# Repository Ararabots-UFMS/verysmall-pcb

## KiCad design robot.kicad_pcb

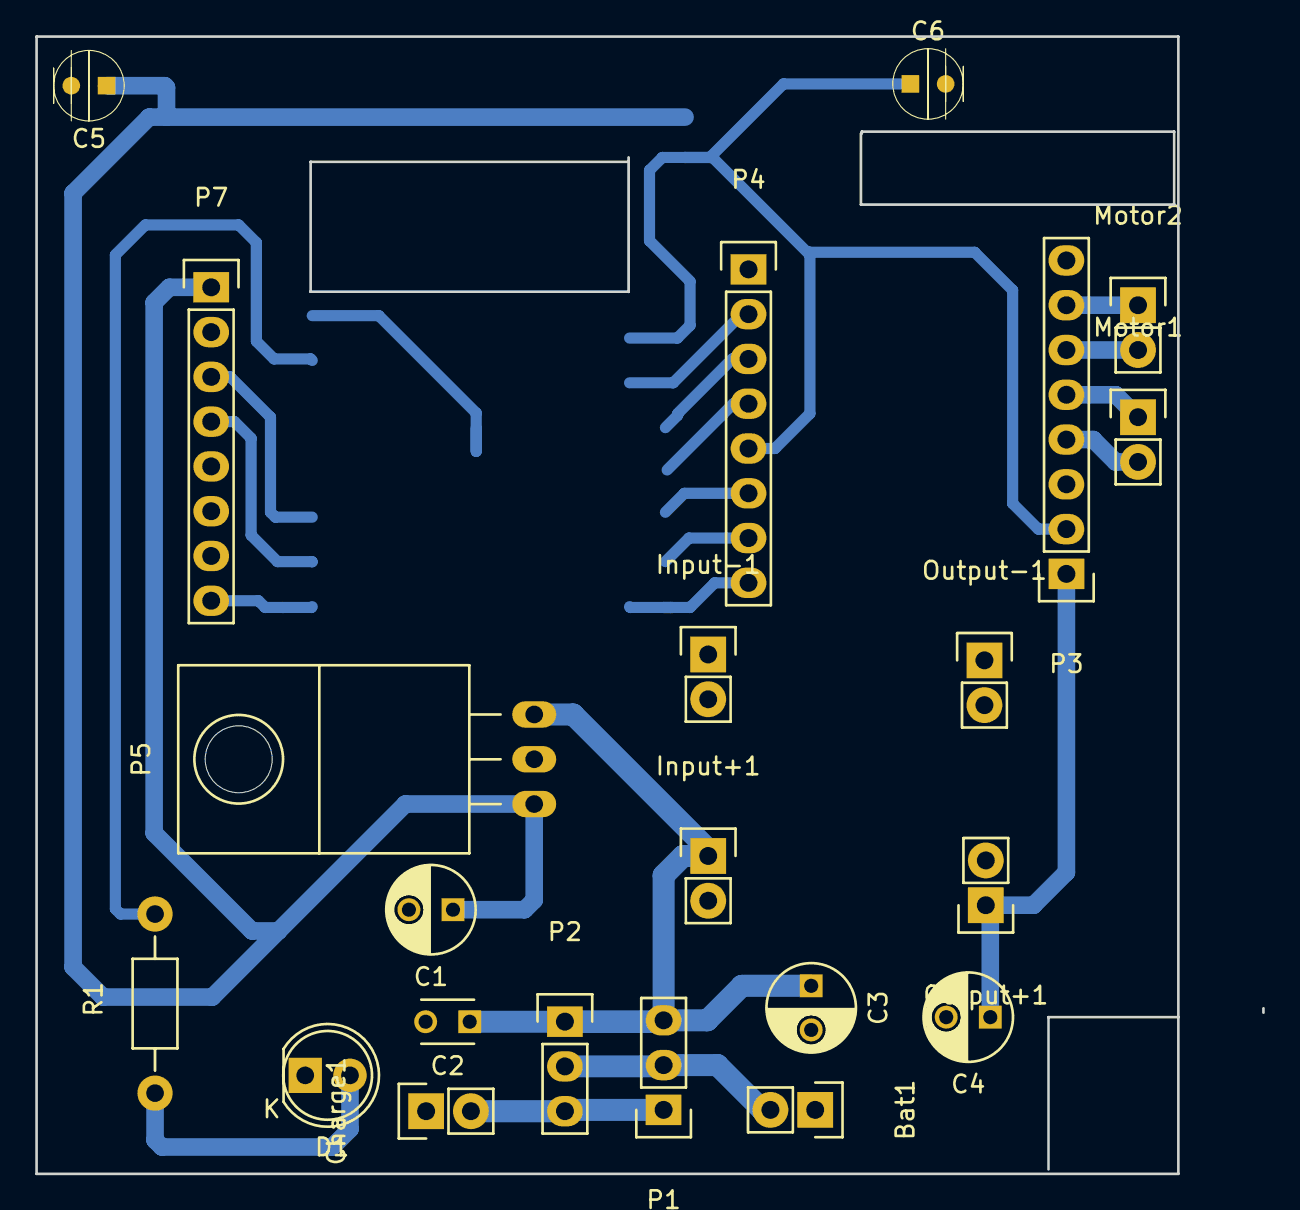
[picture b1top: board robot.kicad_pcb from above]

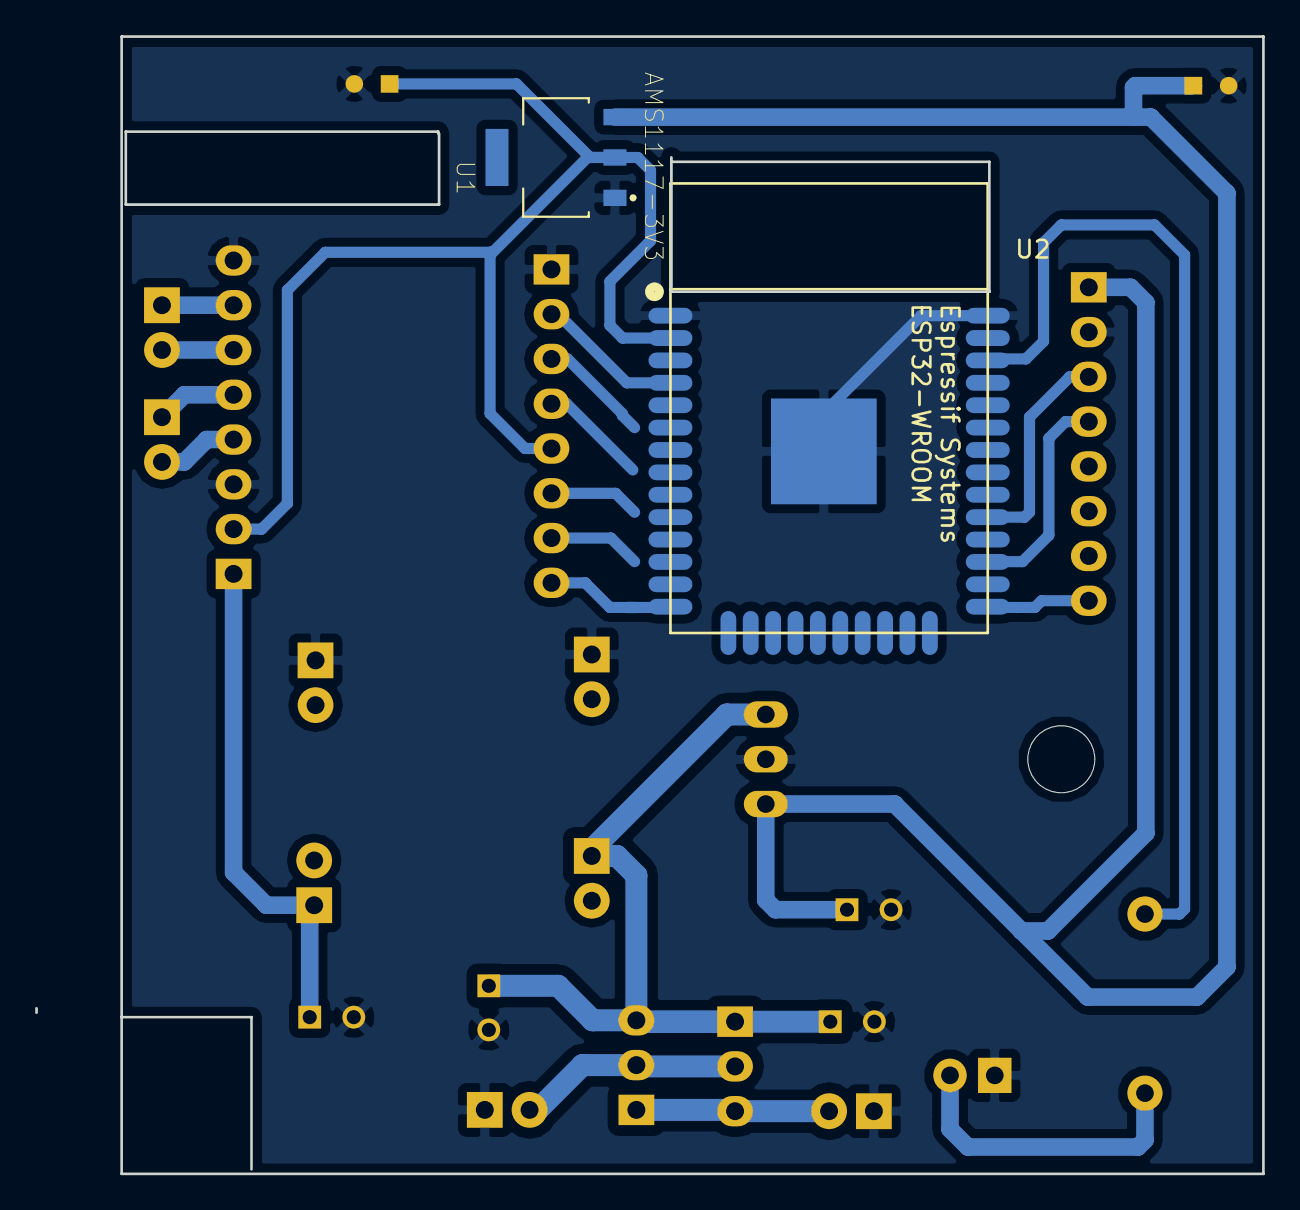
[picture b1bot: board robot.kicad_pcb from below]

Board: 2 copper layers, 69.6 x 64.5 mm, 24 parts (2 on the bottom side), 18 nets.

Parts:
Bat1: CONN_01X02; Pin_Header_Straight_1x02
C1: 33uF; C_Radial_D5_L6_P2.5
C2: 100nF; C_Disc_D3_P2.5
C3, C5: 100uF; C_Radial_D5_L11_P2.5
C4, C6: 10uF; C_Radial_D5_L11_P2.5
Charge1: CONN_01X02; Pin_Header_Straight_1x02
D1: LED; LED-5MM
Input+1: CONN_01X02; Pin_Header_Straight_1x02
Input-1: CONN_01X02; Pin_Header_Straight_1x02
Motor1, Motor2: CONN_01X02; Pin_Header_Straight_1x02
Output+1: CONN_01X02; Pin_Header_Straight_1x02
Output-1: CONN_01X02; Pin_Header_Straight_1x02
P1, P2: CONN_01X03; Pin_Header_Straight_1x03
P3, P4, P7: CONN_01X08; Pin_Header_Straight_1x08
P5: CONN_01X03; TO-220_Neutral123_Horizontal
R1: 220; Resistor_Horizontal_RM10mm
U1: AMS1117-3V3; SOT229P700X180-4N
U2: ESP32-WROOM

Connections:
GND: Bat1.1, C1.2, C2.2, C3.2, C4.2, C5.2, C6.2, Charge1.1, D1.1, Input-1.1, Output-1.1, P3.3, P3.8, P4.1, P5.2, P7.2, U1.1, U2.1, U2.38, U2.39
INT: P7.8, U2.25
LED: R1.2, U2.36
unnamed: Bat1.2, P1.2, P2.2
unnamed: C1.1, C5.1, P5.1, P7.1, U1.3
unnamed: Charge1.2, P1.1, P2.3
unnamed: D1.2, R1.1
unnamed: Motor1.1, P3.5
unnamed: Motor1.2, P3.4
unnamed: Motor2.1, P3.7
unnamed: Motor2.2, P3.6
PWMA: P4.8, U2.14
PWMB: P4.2, U2.4
SCL: P7.3, U2.29
SDA: P7.4, U2.27
VM: C4.1, Output+1.1, P3.1
Vcc: C6.1, P3.2, P4.5, U1.2, U2.2
Vin: C2.1, C3.1, Input+1.1, P1.3, P2.1, P5.3

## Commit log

2018-07-27 Adição do primeiro modelo de placa, necessário modificações.
2018-08-02 Ajuste na face do esp
2018-08-07 mudanças na dimensão da placa.
2018-08-08 corrigir gnd da ponte H
2018-08-11 eagle
2018-08-13 falta conferir pinagem ponte h
2018-08-13 falta conferir pinagem ponte h adicao led
2018-08-13 Adição dos pinos dos motores e do switch button
2018-08-18 Esquematico pronto
2018-08-18 Esquematico sem diodo
2018-08-19 ajuste de lable
2018-09-01 utlima versao plava
2018-10-12 atualizando
2019-09-24 deleting unnecessary files
